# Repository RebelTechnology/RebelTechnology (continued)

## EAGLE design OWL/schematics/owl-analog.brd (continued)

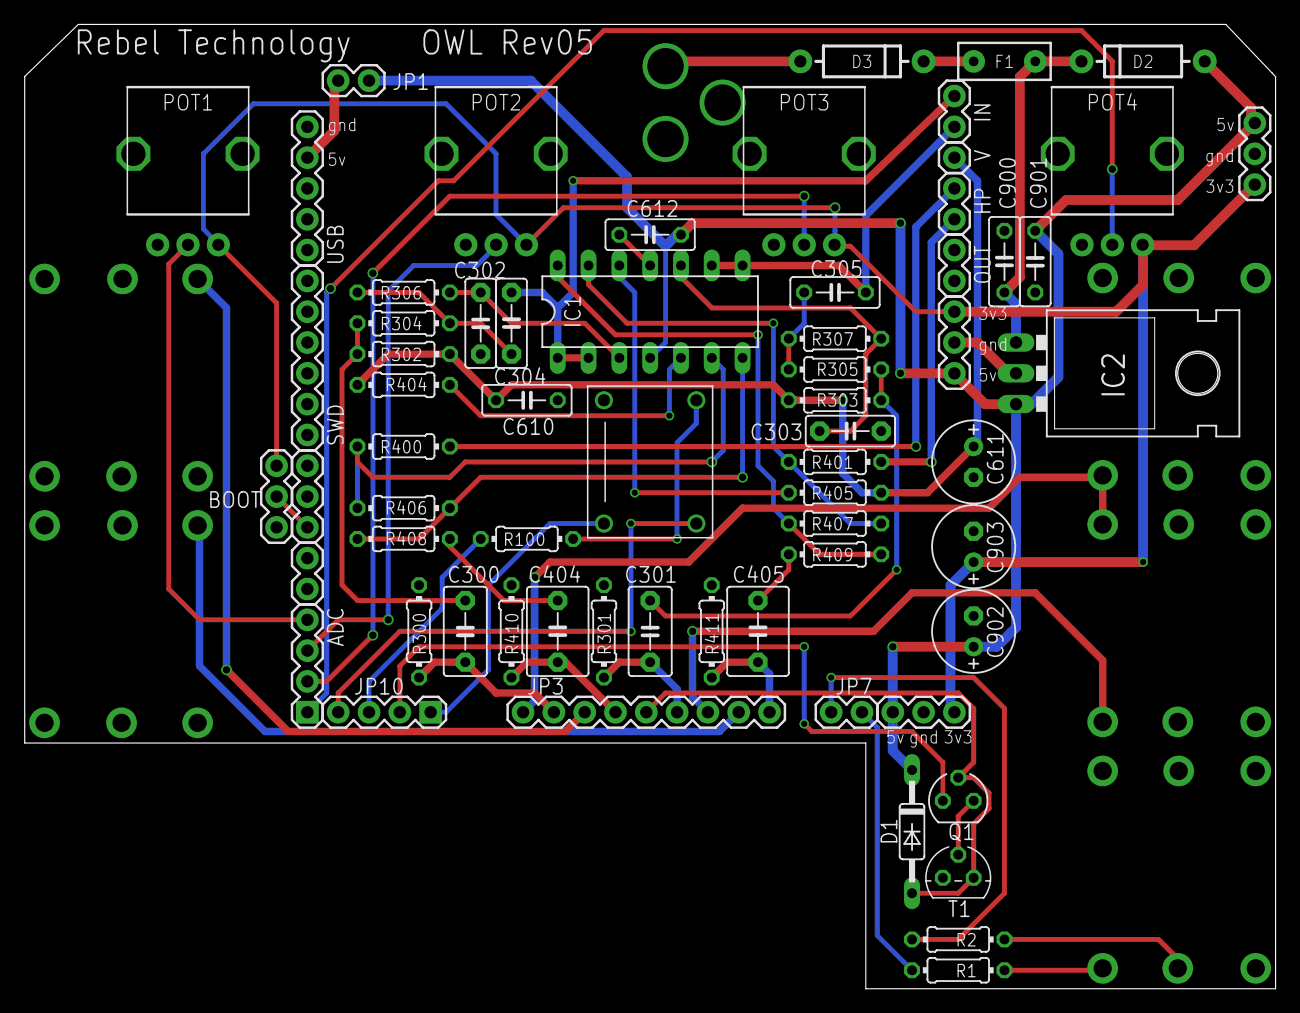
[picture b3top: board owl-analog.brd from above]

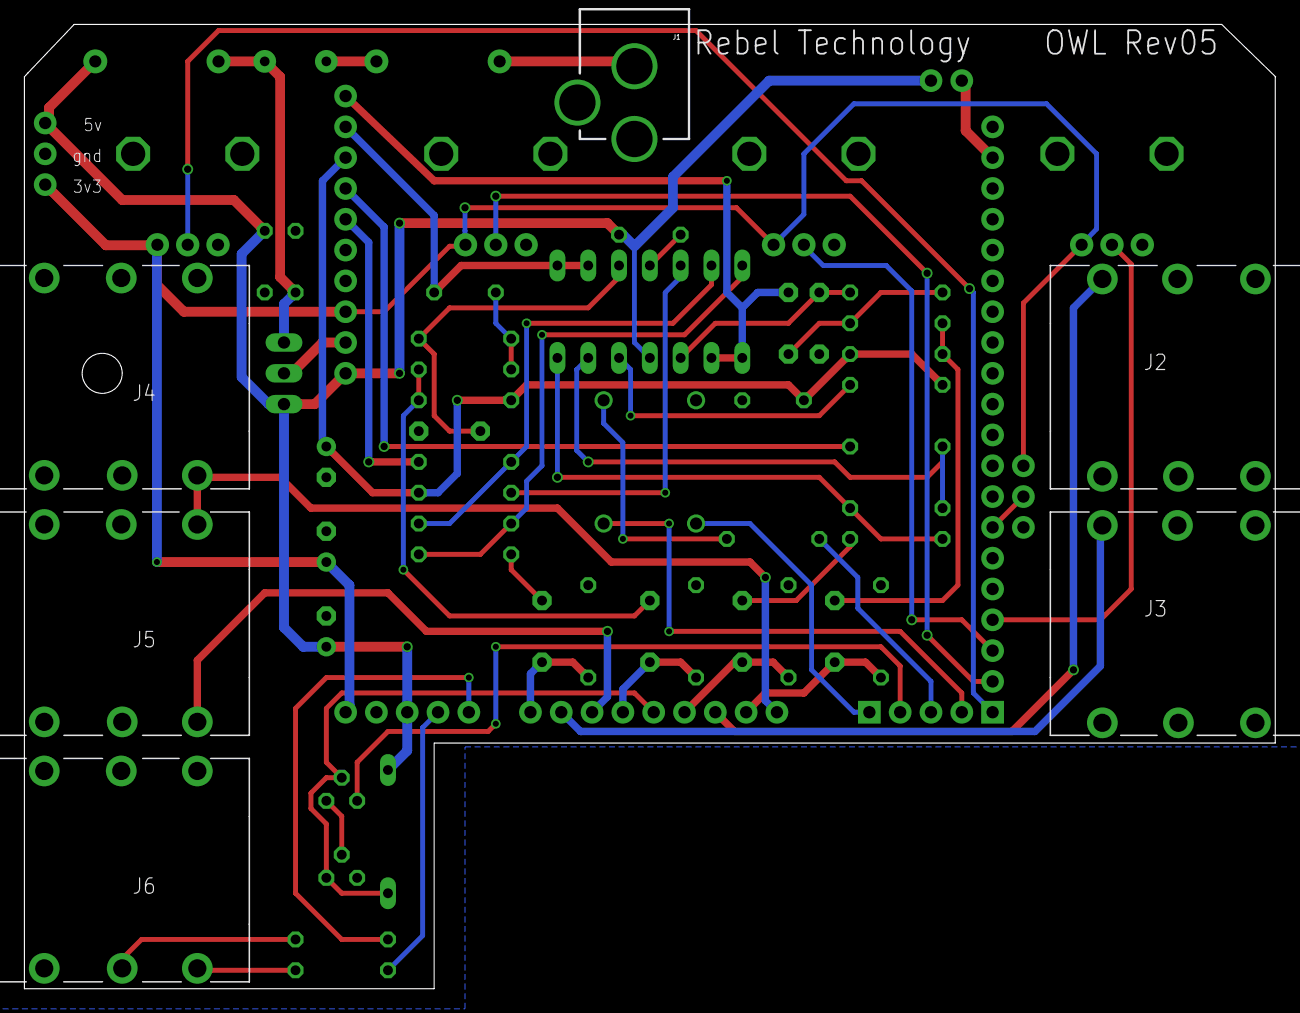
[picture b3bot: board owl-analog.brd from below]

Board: 2 copper layers, 103.1 x 79.5 mm, 72 parts (6 on the bottom side), 49 nets.

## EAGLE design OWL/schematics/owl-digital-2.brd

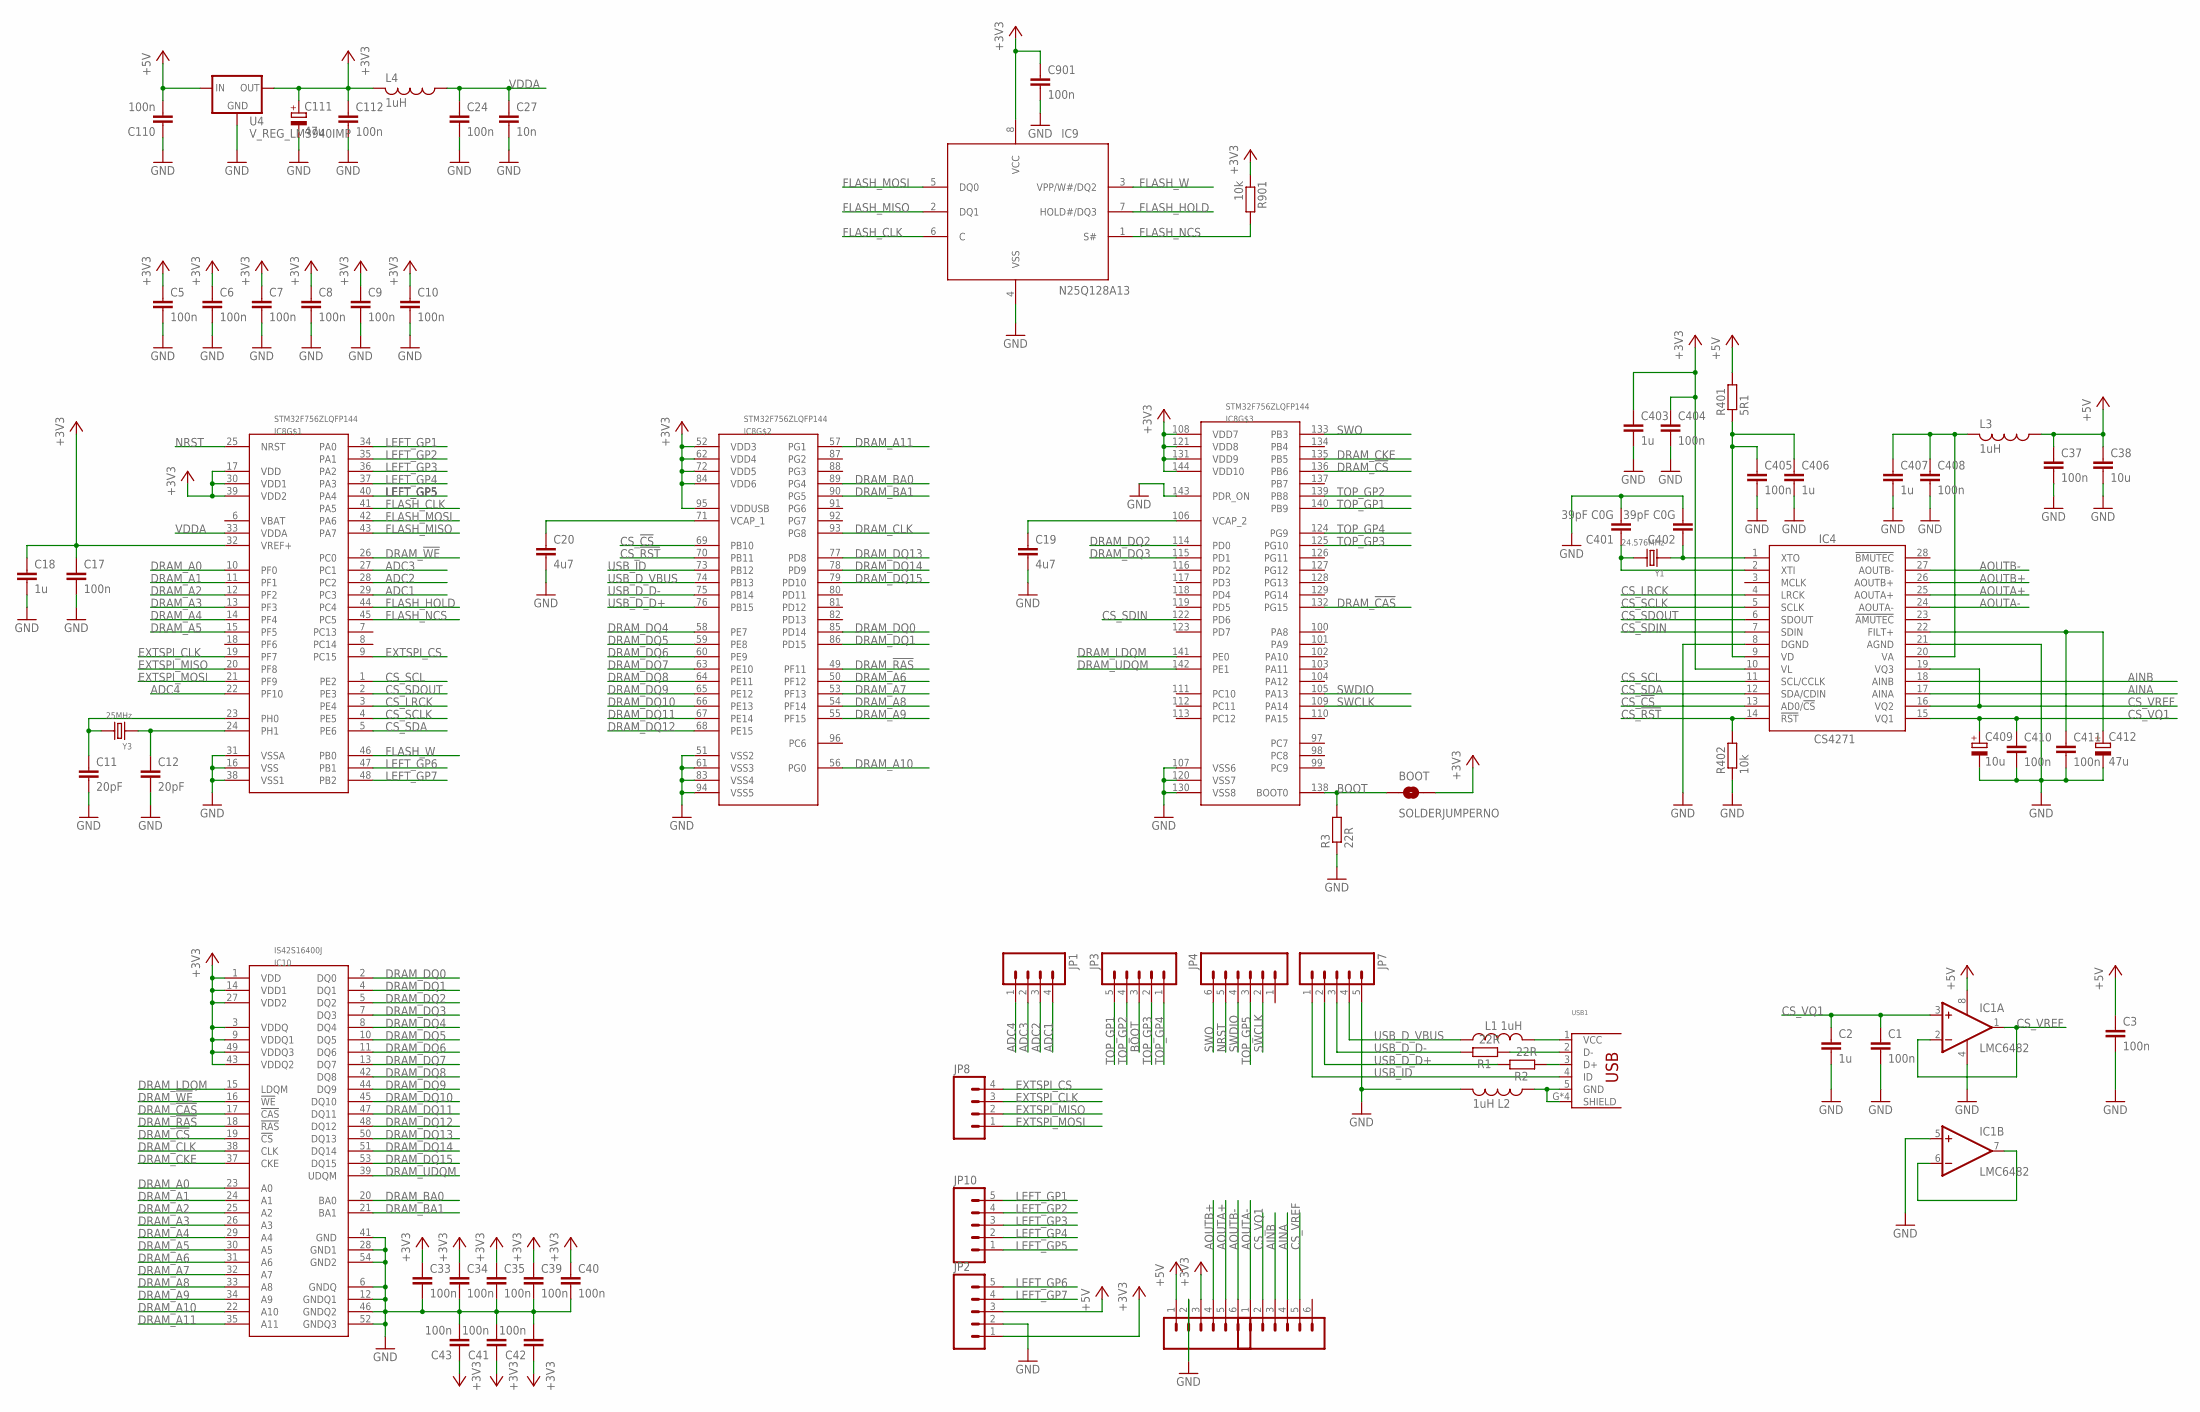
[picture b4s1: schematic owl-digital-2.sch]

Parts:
BOOT: SOLDERJUMPERNO; SJ_2S-NO
C1, C3, C5, C6, C7, C8, C9, C10, C17, C24, C33, C34, C35, C37, C39, C40, C41, C42, C43, C110, C112, C404, C405, C408, C410, C411, C901: 100n; C0603
C2, C18, C403, C406, C407: 1u; C0603
C11, C12: 20pF; C0603
C19, C20: 4u7; C0603
C27: 10n; C0603
C38: 10u; C1206
C111, C412: 47u; CPOL-5
C401, C402: 39pF C0G; C0603
C409: 10u; CPOL-5
IC1: LMC6482; SO08
IC4: CS4271; TSSOP28-0.65-9.7X4.4MM
IC8: STM32F756ZLQFP144; QFP50P2200X2200X160-144N
IC9: N25Q128A13; SO8W
IC10: IS42S16400J; TSOP54-400
JP1, JP8: M04PTH; 1X04
JP2, JP3, JP7, JP10: M05PTH; 1X05
JP4, JP5, JP6: M06SIP; 1X06
L1, L2, L3, L4: 1uH; 0603
R1, R2, R3: 22R; 0603
R401: 5R1; 0603
R402, R901: 10k; 0603
U4: V_REG_LM3940IMP; SOT223
USB1: USB_HRS_ZX62-B-5PA(11)MICRO.B; HRS_ZX62RD-AB-5P8
Y1: 24.576MHz; X2-SMD-5.0X3.2X1.3MM
Y3: 25MHz; X2-SMD-5.0X3.2X1.3MM

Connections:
+3V3: BOOT.2, C5.1, C6.1, C7.1, C8.1, C9.1, C10.1, C17.1, C18.1, C33.1, C34.1, C35.1, C39.1, C40.1, C41.1, C42.1, C43.1, C111.+, C112.1, C403.1, C404.1, C901.1, IC4.10 (VL), IC8.17 (VDD), IC8.30 (VDD1), IC8.32 (VREF+), IC8.39 (VDD2), IC8.52 (VDD3), IC8.62 (VDD4), IC8.72 (VDD5), IC8.84 (VDD6), IC8.95 (VDDUSB), IC8.108 (VDD7), IC8.121 (VDD8), IC8.131 (VDD9), IC8.144 (VDD10), IC9.8 (VCC), IC10.1 (VDD), IC10.3 (VDDQ), IC10.9 (VDDQ1), IC10.14 (VDD1), IC10.27 (VDD2), IC10.43 (VDDQ2), IC10.49 (VDDQ3), JP2.1, JP5.3, L4.2, R901.1, U4.3 (OUT)
+5V: C3.1, C37.1, C38.1, C110.2, IC1.8 (V+), JP2.3, JP5.1, L3.1, R401.2, U4.1 (IN)
ADC1: IC8.29 (PC3), JP1.4
ADC2: IC8.28 (PC2), JP1.3
ADC3: IC8.27 (PC1), JP1.2
ADC4: IC8.22 (PF10), JP1.1
AINA: IC4.17 (AINA), JP6.4
AINB: IC4.18 (AINB), JP6.3
AOUTA+: IC4.25 (AOUTA+), JP5.5
AOUTA-: IC4.24 (AOUTA-), JP6.1
AOUTB+: IC4.26 (AOUTB+), JP5.4
AOUTB-: IC4.27 (AOUTB-), JP5.6
BOOT: BOOT.1, IC8.138 (BOOT0), JP3.3, R3.2
CS_!CS: IC4.13 (AD0/!CS), IC8.69 (PB10)
CS_!RST: IC4.14 (!RST), IC8.70 (PB11), R402.2
CS_LRCK: IC4.4 (LRCK), IC8.3 (PE4)
CS_SCL: IC4.11 (SCL/CCLK), IC8.1 (PE2)
CS_SCLK: IC4.5 (SCLK), IC8.4 (PE5)
CS_SDA: IC4.12 (SDA/CDIN), IC8.5 (PE6)
CS_SDIN: IC4.7 (SDIN), IC8.122 (PD6)
CS_SDOUT: IC4.6 (SDOUT), IC8.2 (PE3)
CS_VQ1: C1.1, C2.1, C409.+, C410.1, IC1.3 (+IN), IC4.15 (VQ1), JP6.2
CS_VREF: IC1.1 (OUT), IC1.2 (-IN), IC4.16 (VQ2), IC4.19 (VQ3), JP6.5
DRAM_!CAS: IC8.132 (PG15), IC10.17 (!CAS)
DRAM_!CS: IC8.136 (PB6), IC10.19 (!CS)
DRAM_!RAS: IC8.49 (PF11), IC10.18 (!RAS)
DRAM_!WE: IC8.26 (PC0), IC10.16 (!WE)
DRAM_A0: IC8.10 (PF0), IC10.23 (A0)
DRAM_A1: IC8.11 (PF1), IC10.24 (A1)
DRAM_A2: IC8.12 (PF2), IC10.25 (A2)
DRAM_A3: IC8.13 (PF3), IC10.26 (A3)
DRAM_A4: IC8.14 (PF4), IC10.29 (A4)
DRAM_A5: IC8.15 (PF5), IC10.30 (A5)
DRAM_A6: IC8.50 (PF12), IC10.31 (A6)
DRAM_A7: IC8.53 (PF13), IC10.32 (A7)
DRAM_A8: IC8.54 (PF14), IC10.33 (A8)
DRAM_A9: IC8.55 (PF15), IC10.34 (A9)
DRAM_A10: IC8.56 (PG0), IC10.22 (A10)
DRAM_A11: IC8.57 (PG1), IC10.35 (A11)
DRAM_BA0: IC8.89 (PG4), IC10.20 (BA0)
DRAM_BA1: IC8.90 (PG5), IC10.21 (BA1)
DRAM_CKE: IC8.135 (PB5), IC10.37 (CKE)
DRAM_CLK: IC8.93 (PG8), IC10.38 (CLK)
DRAM_DQ0: IC8.85 (PD14), IC10.2 (DQ0)
DRAM_DQ1: IC8.86 (PD15), IC10.4 (DQ1)
DRAM_DQ2: IC8.114 (PD0), IC10.5 (DQ2)
DRAM_DQ3: IC8.115 (PD1), IC10.7 (DQ3)
DRAM_DQ4: IC8.58 (PE7), IC10.8 (DQ4)
DRAM_DQ5: IC8.59 (PE8), IC10.10 (DQ5)
DRAM_DQ6: IC8.60 (PE9), IC10.11 (DQ6)
DRAM_DQ7: IC8.63 (PE10), IC10.13 (DQ7)
DRAM_DQ8: IC8.64 (PE11), IC10.42 (DQ8)
DRAM_DQ9: IC8.65 (PE12), IC10.44 (DQ9)
DRAM_DQ10: IC8.66 (PE13), IC10.45 (DQ10)
DRAM_DQ11: IC8.67 (PE14), IC10.47 (DQ11)
DRAM_DQ12: IC8.68 (PE15), IC10.48 (DQ12)
DRAM_DQ13: IC8.77 (PD8), IC10.50 (DQ13)
DRAM_DQ14: IC8.78 (PD9), IC10.51 (DQ14)
DRAM_DQ15: IC8.79 (PD10), IC10.53 (DQ15)
DRAM_LDQM: IC8.141 (PE0), IC10.15 (LDQM)
DRAM_UDQM: IC8.142 (PE1), IC10.39 (UDQM)
EXTSPI_CLK: IC8.19 (PF7), JP8.3
EXTSPI_CS: IC8.9 (PC15), JP8.4
EXTSPI_MISO: IC8.20 (PF8), JP8.2
EXTSPI_MOSI: IC8.21 (PF9), JP8.1
FLASH_CLK: IC8.41 (PA5), IC9.6 (C)
FLASH_HOLD: IC8.44 (PC4), IC9.7 (HOLD#/DQ3)
FLASH_MISO: IC8.43 (PA7), IC9.2 (DQ1)
FLASH_MOSI: IC8.42 (PA6), IC9.5 (DQ0)
FLASH_NCS: IC8.45 (PC5), IC9.1 (S#), R901.2
FLASH_W: IC8.46 (PB0), IC9.3 (VPP/W#/DQ2)
GND: C1.2, C2.2, C3.2, C5.2, C6.2, C7.2, C8.2, C9.2, C10.2, C11.2, C12.2, C17.2, C18.2, C19.2, C20.2, C24.2, C27.2, C33.2, C34.2, C35.2, C37.2, C38.2, C39.2, C40.2, C41.2, C42.2, C43.2, C110.1, C111.-, C112.2, C401.2, C402.2, C403.2, C404.2, C405.2, C406.2, C407.2, C408.2, C409.-, C410.2, C411.2, C412.-, C901.2, IC1.4 (V-), IC1.5 (+IN), IC4.8 (DGND), IC4.21 (AGND), IC8.16 (VSS), IC8.31 (VSSA), IC8.38 (VSS1), IC8.51 (VSS2), IC8.61 (VSS3), IC8.83 (VSS4), IC8.94 (VSS5), IC8.107 (VSS6), IC8.120 (VSS7), IC8.130 (VSS8), IC8.143 (PDR_ON), IC9.4 (VSS), IC10.6 (GNDQ), IC10.12 (GNDQ1), IC10.28 (GND1), IC10.41 (GND), IC10.46 (GNDQ2), IC10.52 (GNDQ3), IC10.54 (GND2), JP2.2, JP5.2, JP7.5, L2.2, R3.1, R402.1, U4.2 (GND)
LEFT_GP1: IC8.34 (PA0), JP10.5
LEFT_GP2: IC8.35 (PA1), JP10.4
LEFT_GP3: IC8.36 (PA2), JP10.3
LEFT_GP4: IC8.37 (PA3), JP10.2
LEFT_GP5: IC8.40 (PA4), JP10.1
LEFT_GP6: IC8.47 (PB1), JP2.5
LEFT_GP7: IC8.48 (PB2), JP2.4
unnamed: L2.1, USB1.5 (GND), USB1.G (SHIELD), USB1.G2 (SHIELD), USB1.G3 (SHIELD), USB1.G4 (SHIELD)
unnamed: L1.2, USB1.1 (VCC)
unnamed: IC1.6 (-IN), IC1.7 (OUT)
unnamed: R2.1, USB1.3 (D+)
unnamed: R1.1, USB1.2 (D-)
unnamed: C12.1, IC8.24 (PH1), Y3.1
unnamed: C11.1, IC8.23 (PH0), Y3.2
unnamed: C402.1, IC4.1 (XTO), Y1.1
unnamed: C411.1, C412.+, IC4.22 (FILT+)
unnamed: C401.1, IC4.2 (XTI), Y1.2
unnamed: C19.1, IC8.106 (VCAP_2)
unnamed: C20.1, IC8.71 (VCAP_1)
NRST: IC8.25 (NRST), JP4.5
SWCLK: IC8.109 (PA14), JP4.2
SWDIO: IC8.105 (PA13), JP4.4
SWO: IC8.133 (PB3), JP4.6
TOP_GP1: IC8.140 (PB9), JP3.5
TOP_GP2: IC8.139 (PB8), JP3.4
TOP_GP3: IC8.125 (PG10), JP3.2
TOP_GP4: IC8.124 (PG9), JP3.1
TOP_GP5: JP4.3
USB_D_D+: IC8.76 (PB15), JP7.2, R2.2
USB_D_D-: IC8.75 (PB14), JP7.3, R1.2
USB_D_VBUS: IC8.74 (PB13), JP7.4, L1.1
USB_ID: IC8.73 (PB12), JP7.1, USB1.4 (ID)
VA: C407.1, C408.1, IC4.20 (VA), L3.2
VD: C405.1, C406.1, IC4.9 (VD), R401.1
VDDA: C24.1, C27.1, IC8.33 (VDDA), L4.1

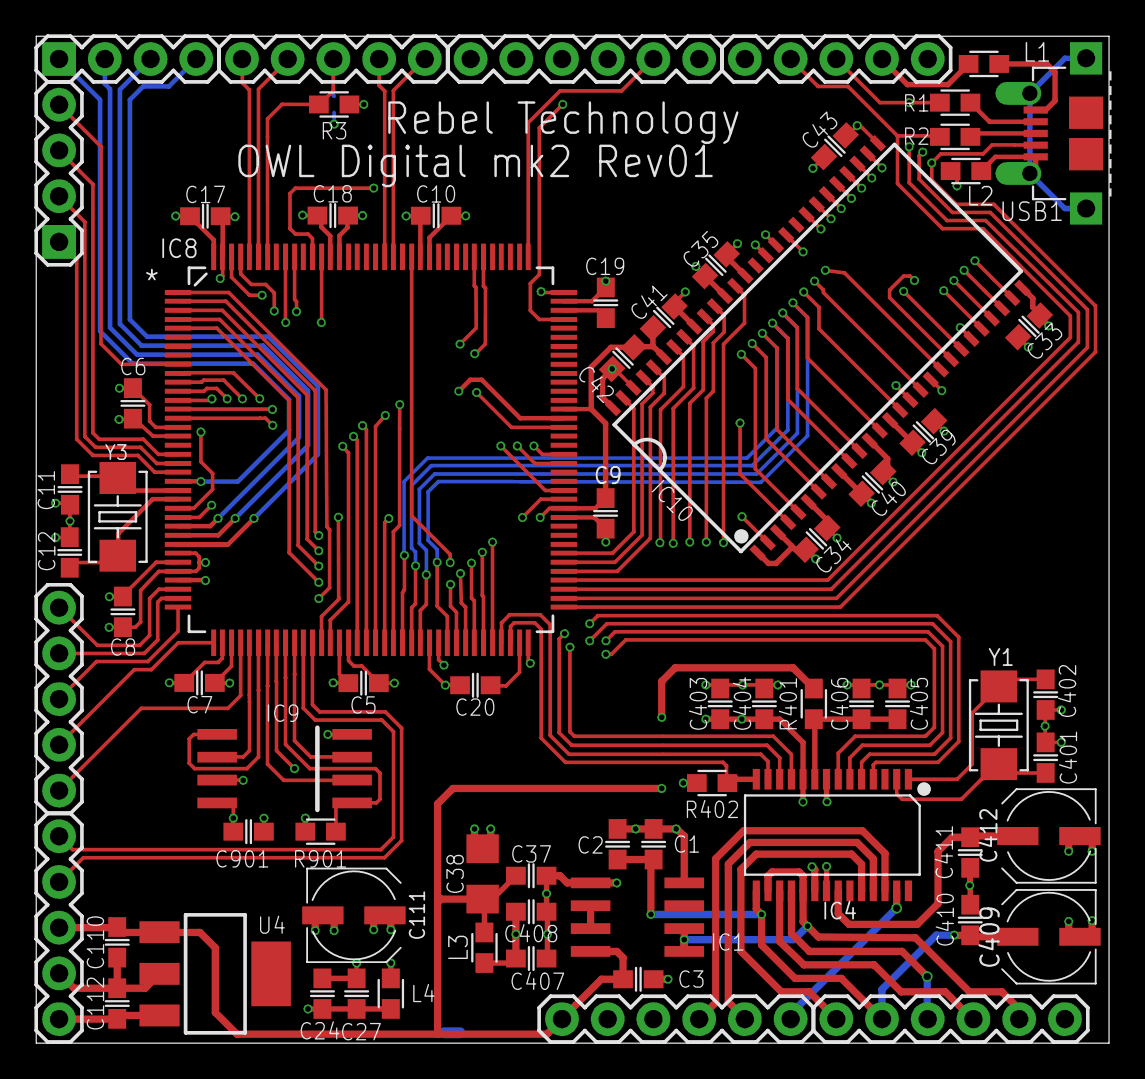
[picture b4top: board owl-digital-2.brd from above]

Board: 4 copper layers, 59.6 x 55.9 mm, 72 parts (1 on the bottom side), 106 nets.
